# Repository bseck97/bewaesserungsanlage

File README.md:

# Automatische Bewässerungsanlage

## Beschreibung

Automatische Bewässerungsanlage bestehend aus einer Basisstation mit einem ESP32 und kapazitiven Bodenfeuchtesensoren.

Die Bewässerungsanlage ist im Rahmen eines Masterprojekts der [Hochschule Heilbronn](https://www.hs-heilbronn.de/) entstanden. Die Entwicklung und die Messungen fanden im Labor für Elektronische Schaltungstechnik statt. 

Für weitere Informationen wird auf die [Dokumentation](./dokumentation.pdf) verwiesen. 

## Dateistruktur

- basisstation - ESP-IDF Projekt für die Basisstation
- sensor - STM32CubeMX Projekt für den Sensor
- sensor_pcb - EAGLE Projekt für das Sensorboard

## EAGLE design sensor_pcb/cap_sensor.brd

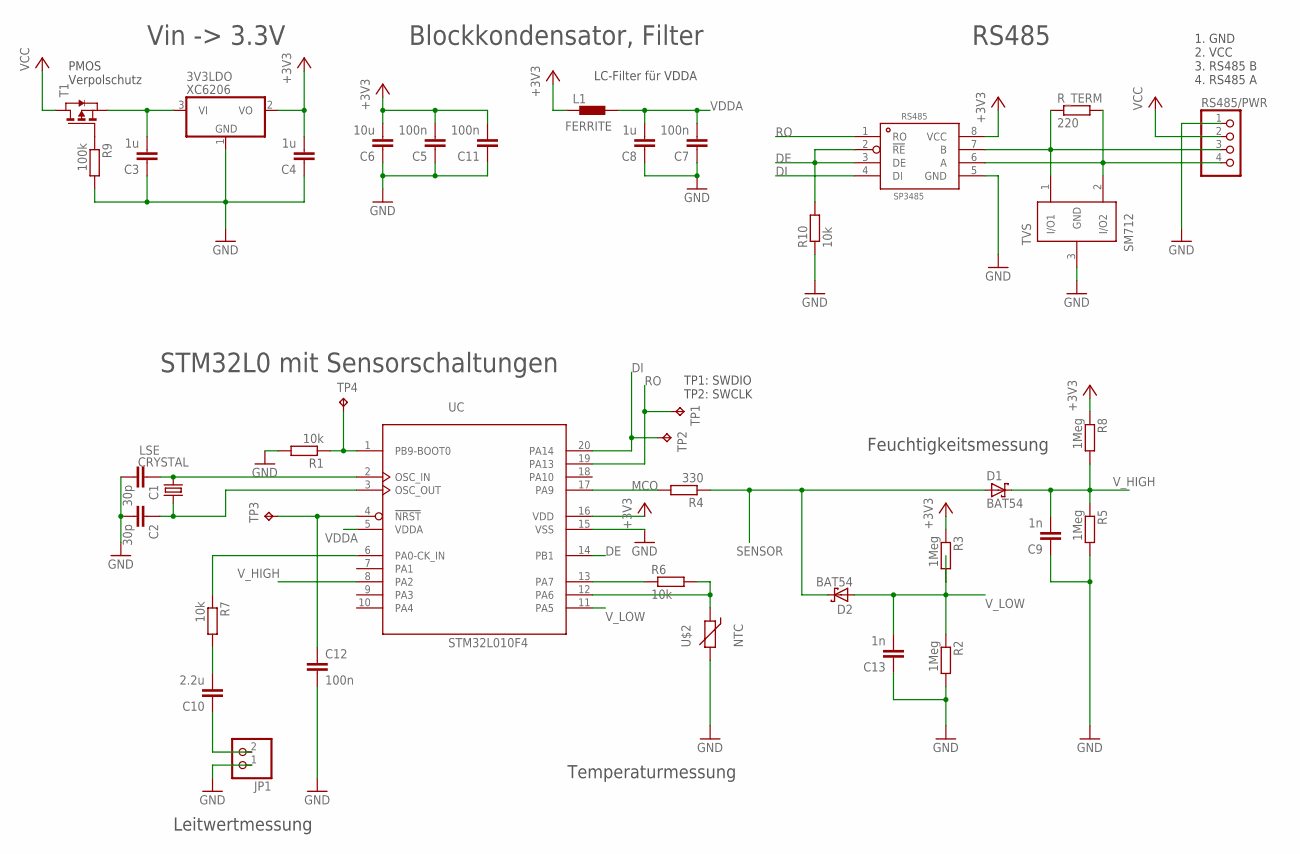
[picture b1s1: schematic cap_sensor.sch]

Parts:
3V3LDO: XC6206; SOT23-3
C1, C2: 30p; C0603
C3, C4, C8: 1u; C0603
C5, C7, C11, C12: 100n; C0603
C6: 10u; C0603
C9, C13: 1n; C0603
C10: 2.2u; C0603
D1, D2: BAT54; SOT23
JP1: PINHD-1X2; 1X02
L1: FERRITE; R0603
LSE: CRYSTAL; CRYSTAL-3.2X1.5
R1, R6, R7, R10: 10k; R0603
R2, R3, R5, R8: 1Meg; R0603
R4: 330; R0603
R9: 100k; R0603
RS485: SP3485; NSOIC8
RS485/PWR: PINHD-1X4; 1X04
R_TERM: 220; R0603
T1: PMOSSOT23; SOT-23
TP1, TP2, TP3, TP4: TPTP12R; TP12R
TVS: SM712; SOT23-3
U$2: NTC; R0603
UC: STM32L010F4; TSSOP20-I

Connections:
+3V3: 3V3LDO.2 (VO), C4.2, C5.2, C6.2, C11.2, L1.1, R3.1, R8.1, RS485.8 (VCC), UC.16 (VDD)
DE: R10.2, RS485.2 (!RE), RS485.3 (DE), UC.14 (PB1)
DI: RS485.4 (DI), TP2.TP, UC.20 (PA14)
GND: 3V3LDO.1 (GND), C1.2, C2.2, C3.1, C4.1, C5.1, C6.1, C7.1, C8.1, C9.1, C11.1, C12.2, C13.1, JP1.1, R1.2, R2.2, R5.2, R9.2, R10.1, RS485.5 (GND), RS485/PWR.1, TVS.3 (GND), U$2.2, UC.15 (VSS)
MCO: R4.2, UC.17 (PA9)
unnamed: 3V3LDO.3 (VI), C3.2, T1.2 (S)
unnamed: R1.1, TP4.TP, UC.1 (PB9-BOOT0)
unnamed: R6.1, UC.13 (PA7)
unnamed: C10.1, JP1.2
unnamed: C10.2, R7.2
unnamed: R6.2, U$2.1, UC.12 (PA6)
unnamed: C12.1, TP3.TP, UC.4 (!NRST)
unnamed: C1.1, LSE.1, UC.2 (OSC_IN)
unnamed: C2.1, LSE.2, UC.3 (OSC_OUT)
unnamed: R9.1, T1.3 (G)
unnamed: RS485.7 (B), RS485/PWR.3, R_TERM.1, TVS.1 (I/O1)
unnamed: RS485.6 (A), RS485/PWR.4, R_TERM.2, TVS.2 (I/O2)
RO: RS485.1 (RO), TP1.TP, UC.19 (PA13)
SENSOR: D1.1 (A), D2.3 (C), R4.1
SENS_RES: R7.1, UC.6 (PA0-CK_IN)
VCC: RS485/PWR.2, T1.1 (D)
VDDA: C7.2, C8.2, L1.2, UC.5 (VDDA)
V_HIGH: C9.2, D1.3 (C), R5.1, R8.2, UC.8 (PA2)
V_LOW: C13.2, D2.1 (A), R2.1, R3.2, UC.11 (PA5)

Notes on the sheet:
LC-Filter für VDDA
TP1: SWDIO TP2: SWCLK
PMOS Verpolschutz
Blockkondensator, Filter
Leitwertmessung
Feuchtigkeitsmessung
Temperaturmessung
Vin -> 3.3V
RS485
STM32L0 mit Sensorschaltungen
1. GND 2. VCC 3. RS485 B 4. RS485 A

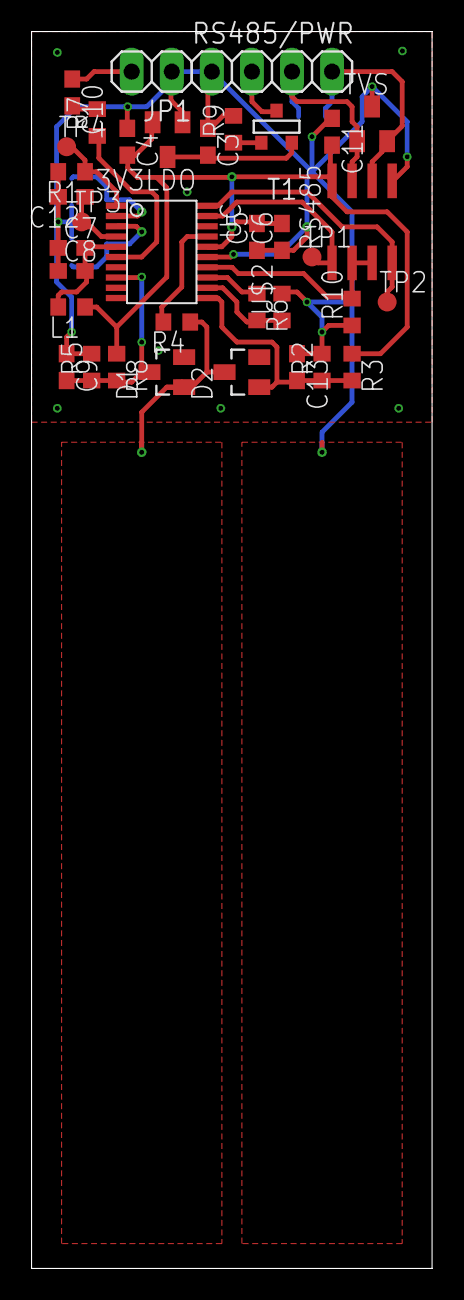
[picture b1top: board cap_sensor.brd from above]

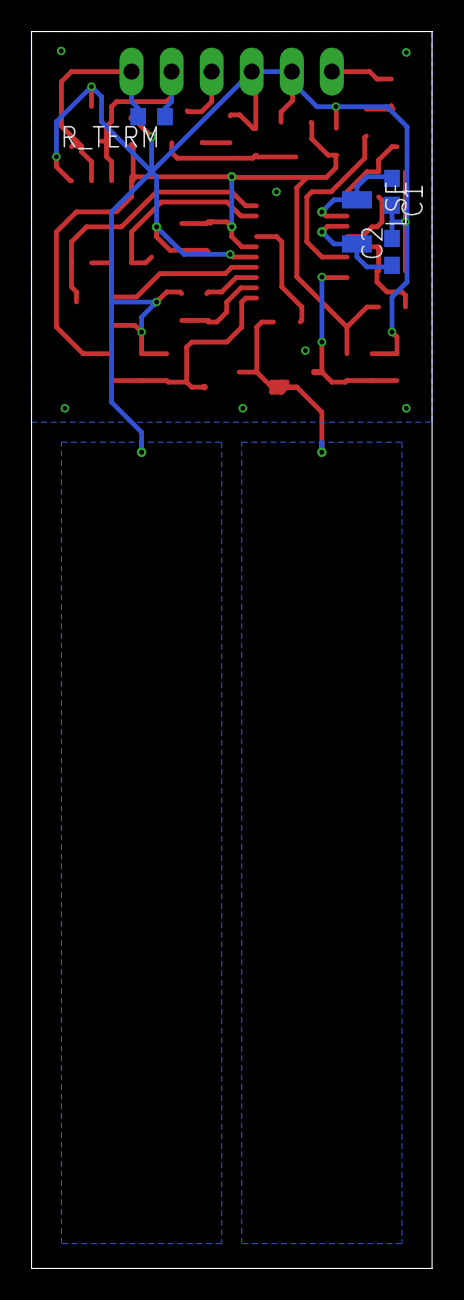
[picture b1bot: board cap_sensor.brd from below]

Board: 2 copper layers, 25.4 x 78.4 mm, 40 parts (4 on the bottom side), 24 nets.

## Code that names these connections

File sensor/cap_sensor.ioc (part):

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Mcu.Name=STM32L010F4Px
Mcu.Package=TSSOP20
Mcu.UserName=STM32L010F4Px
PA0-CK_IN.Mode=IN0
PA0-CK_IN.Signal=ADC_IN0
PA13.Mode=Asynchronous
PA13.Signal=LPUART1_RX
PA14.Mode=Asynchronous
PA14.Signal=LPUART1_TX
PA2.Mode=IN2
PA2.Signal=ADC_IN2
PA5.Mode=IN5
PA5.Signal=ADC_IN5
PA6.Mode=IN6
PA6.Signal=ADC_IN6
PA7.Signal=GPIO_Output
PA9.GPIOParameters=GPIO_Speed
PA9.GPIO_Speed=GPIO_SPEED_FREQ_VERY_HIGH
PA9.Mode=Clock-out
PA9.Signal=RCC_MCO
PB1.Mode=Hardware Flow Control (RS485)
PB1.Signal=LPUART1_DE
RCC.HSE_VALUE=8000000
RCC.SYSCLKFreq_VALUE=2097000
board=custom

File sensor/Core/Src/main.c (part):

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	// first, include ID
	TXData[0] = ID;

	// Configure PA0 as Output and Set it High
	LL_GPIO_SetOutputPin(GPIOA, LL_GPIO_PIN_0);
	LL_GPIO_SetPinMode(GPIOA, LL_GPIO_PIN_0, LL_GPIO_MODE_OUTPUT);

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	// wait 2ms to give the voltage time to stabilize
	HAL_Delay(2);

	// Measure the voltage on PA0
	TXData[1] = Poll_ADC_Channel();

	// Delay for another 8ms to be able to inspect the signal on an oscilloscope
	HAL_Delay(8);

	// Manually set PA0 LOW to discharge the capacitor
	LL_GPIO_ResetOutputPin(GPIOA, LL_GPIO_PIN_0);
	LL_GPIO_SetPinMode(GPIOA, LL_GPIO_PIN_0, LL_GPIO_MODE_OUTPUT);

	// measure voltage on PA2 (V_HIGH)
	TXData[2] = Poll_ADC_Channel();

	// measure voltage on PA5 (V_LOW)
	TXData[3] = Poll_ADC_Channel();

	// Set PA7 high (Input R6)
	LL_GPIO_SetOutputPin(GPIOA, LL_GPIO_PIN_7);

	// Delay for 10ms
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	// NTC = Heissleiter, Spannung sinkt bei steigender Temp
	TXData[4] = Poll_ADC_Channel();

	// Set PA7 low
	LL_GPIO_ResetOutputPin(GPIOA, LL_GPIO_PIN_7);

	// Transmit sensor data
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  /* User can add his own implementation to report the HAL error return state */
  __disable_irq();
  while (1) {
	// Configure PA0 as Output and Set it High
	LL_GPIO_SetOutputPin(GPIOA, LL_GPIO_PIN_0);
	LL_GPIO_SetPinMode(GPIOA, LL_GPIO_PIN_0, LL_GPIO_MODE_OUTPUT);
  }
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
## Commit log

2024-03-19 init

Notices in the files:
sensor/Core/Src/main.c:
Copyright (c) 2023 STMicroelectronics.
All rights reserved.
This software is licensed under terms that can be found in the LICENSE file
